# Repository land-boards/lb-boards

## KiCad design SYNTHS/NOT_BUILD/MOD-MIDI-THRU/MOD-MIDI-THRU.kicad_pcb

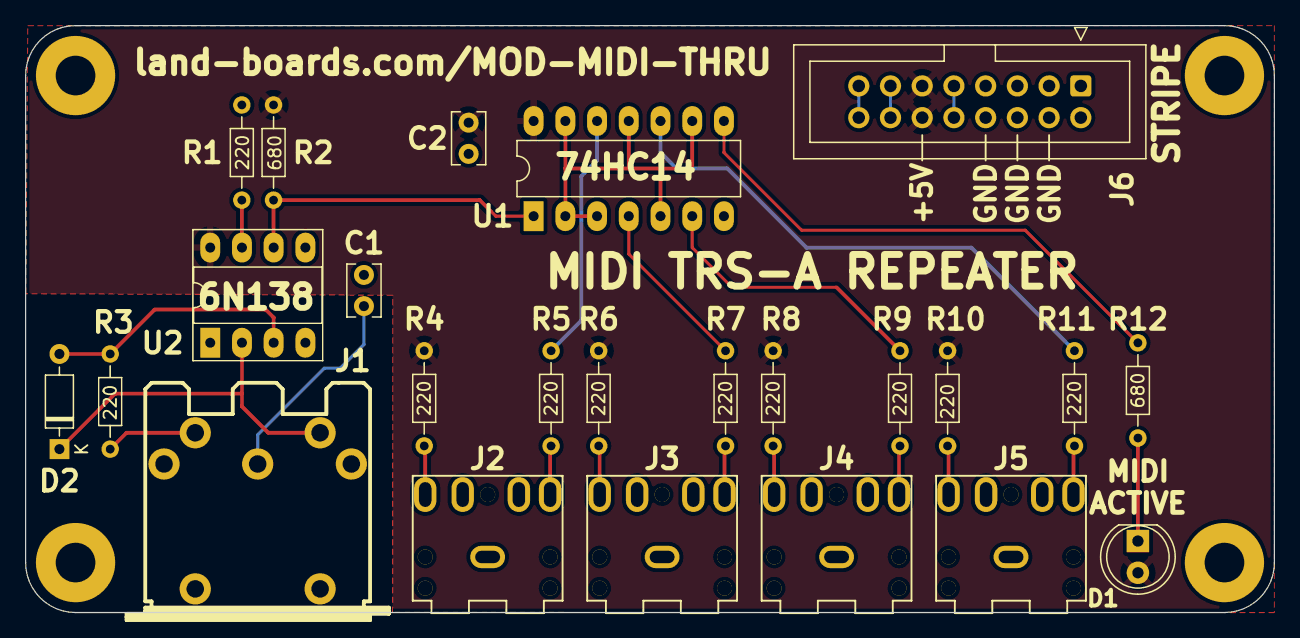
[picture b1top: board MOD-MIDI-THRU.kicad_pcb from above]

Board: 2 copper layers, 100.0 x 47.0 mm, 28 parts (0 on the bottom side), 26 nets.

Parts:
C1, C2: 0.1uF; C_Rect_L4.0mm_W2.5mm_P2.50mm
D1: LED; LED_D5.0mm
D2: 1N914; D_DO-35_SOD27_P7.62mm_Horizontal
J1: DIN-5; MIDI_DIN-5
J2, J3, J4, J5: AudioJack3; Jack_3.5mm_CUI_SJ1-3523N_Horizontal
J6: Conn_02x08_Odd_Even; IDC-Header_2x08_P2.54mm_Vertical
MTG1, MTG2, MTG3, MTG4: MountingHole; MTG-4-40
R1, R3, R4, R5, R6, R7, R8, R9, R10, R11: 220; R_Axial_DIN0204_L3.6mm_D1.6mm_P7.62mm_Horizontal
R2, R12: 680; R_Axial_DIN0204_L3.6mm_D1.6mm_P7.62mm_Horizontal
U1: 74HC14; DIP-14_W7.62mm_LongPads
U2: 6N138; DIP-8_W7.62mm_Socket_LongPads

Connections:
+5V: C2.1, D1.2 (A), J6.11, J6.12, R2.1, R4.1, R6.1, R8.1, R10.1, U1.14 (VCC), U2.8 (VCC)
+12V: J6.9, J6.10
/CV_OUT: J6.13, J6.14
/GATE_OUT: J6.15, J6.16
/MIDI_1_OUT: J2.T, R5.2
/MIDI_1_PWR: J2.R, R4.2
/MIDI_2_OUT: J3.T, R7.2
/MIDI_2_PWR: J3.R, R6.2
/MIDI_3_OUT: J4.T, R9.2
/MIDI_3_PWR: J4.R, R8.2
/MIDI_4_OUT: J5.T, R11.2
/MIDI_4_PWR: J5.R, R10.2
/MIDI_IN: D2.1 (K), J1.4, U2.2 (C1)
/MIDI_RTN: J1.5, R3.2
/RXD: R2.2, U1.1, U2.6 (VO2)
GND: C1.2, C2.2, J2.S, J3.S, J4.S, J5.S, J6.3, J6.4, J6.5, J6.6, J6.7, J6.8, R1.2, U1.7 (GND), U2.5 (GND)
unnamed: C1.1, J1.2
unnamed: D1.1 (K), R12.2
unnamed: D2.2 (A), R3.1, U2.3 (C2)
unnamed: R1.1, U2.7 (VO1)
unnamed: R5.1, U1.12
unnamed: R7.1, U1.4
unnamed: R9.1, U1.6
unnamed: R11.1, U1.10
unnamed: R12.1, U1.8
unnamed: U1.2, U1.3, U1.5, U1.9, U1.11, U1.13

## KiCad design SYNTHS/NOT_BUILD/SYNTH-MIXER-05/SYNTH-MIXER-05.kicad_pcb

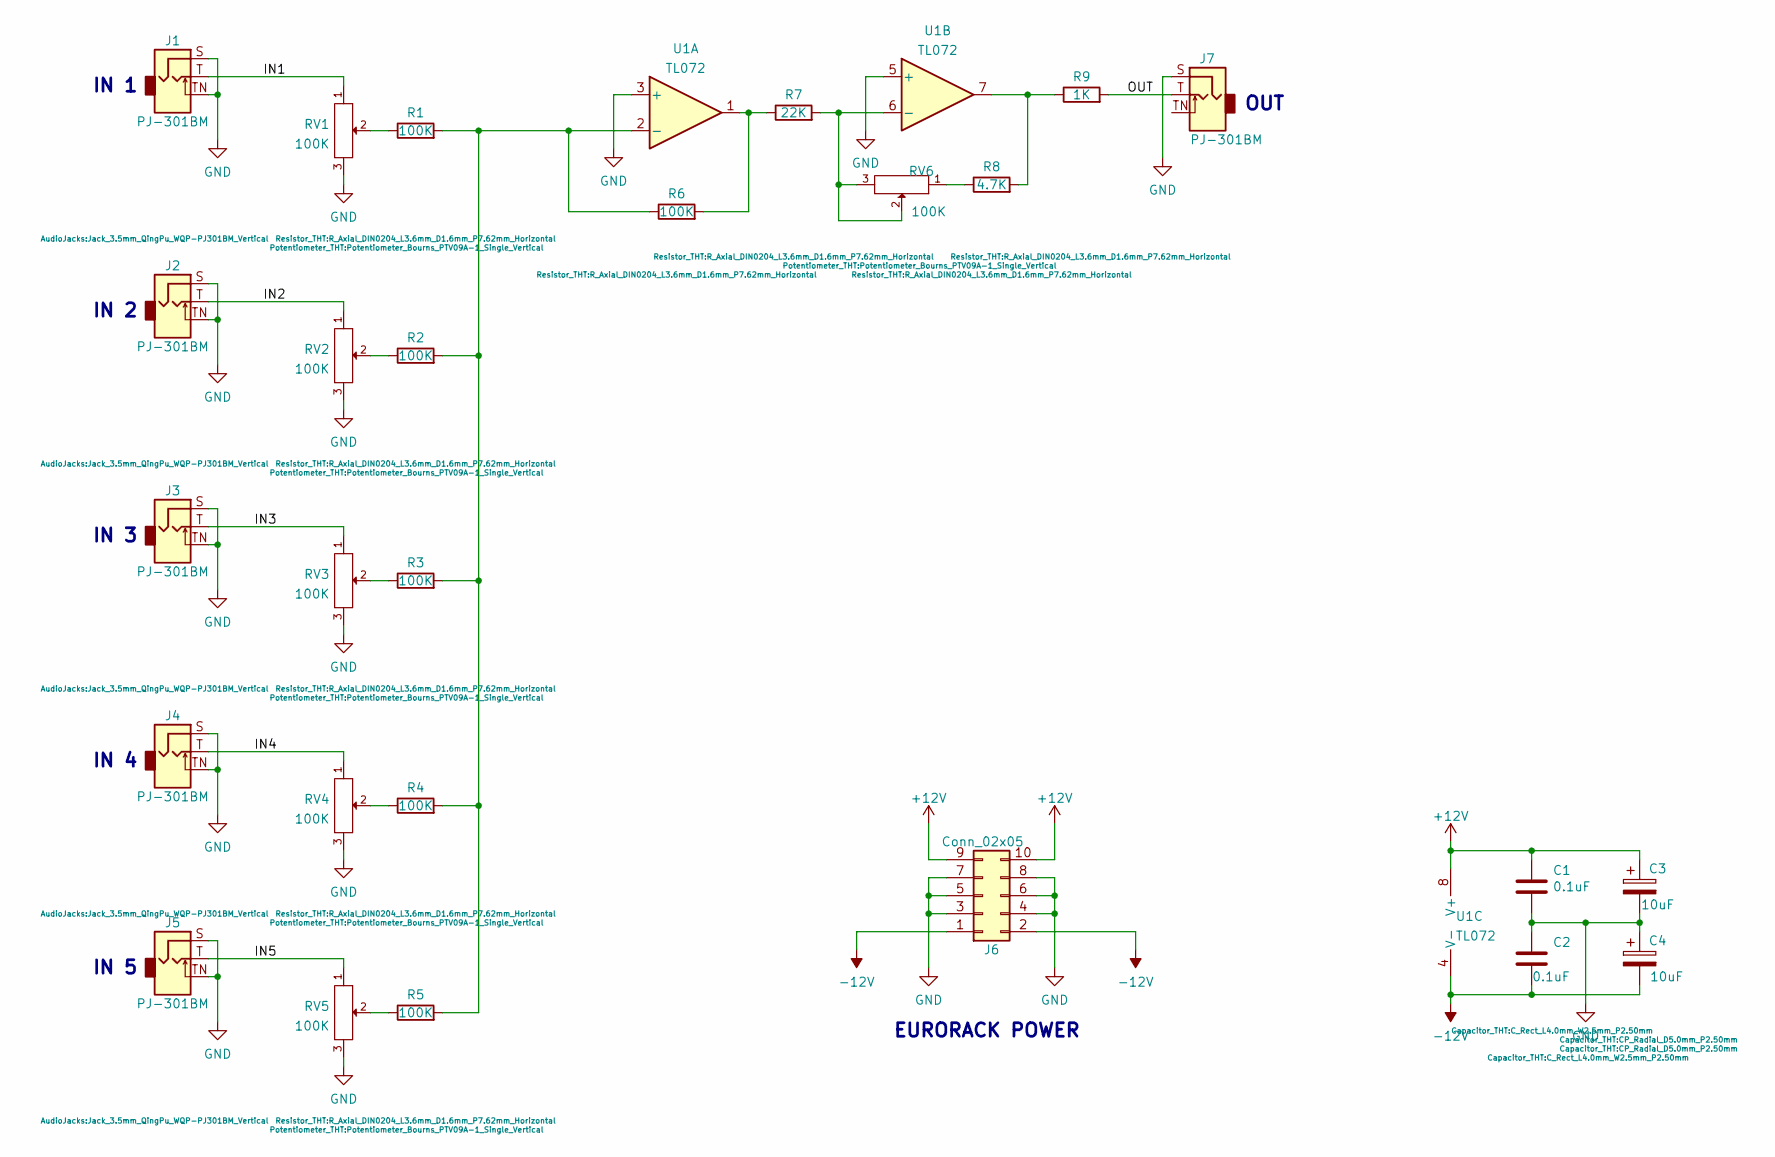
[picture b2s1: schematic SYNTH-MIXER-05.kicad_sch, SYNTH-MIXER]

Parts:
C1, C2: 0.1uF; C_Rect_L4.0mm_W2.5mm_P2.50mm
C3, C4: 10uF; CP_Radial_D5.0mm_P2.50mm
J1, J2, J3, J4, J5, J7: PJ-301BM; Jack_3.5mm_QingPu_WQP-PJ301BM_Vertical
J6: Conn_02x05; IDC-Header_2x05_P2.54mm_Vertical
R1, R2, R3, R4, R5, R6: 100K; R_Axial_DIN0204_L3.6mm_D1.6mm_P7.62mm_Horizontal
R7: 22K; R_Axial_DIN0204_L3.6mm_D1.6mm_P7.62mm_Horizontal
R8: 4.7K; R_Axial_DIN0204_L3.6mm_D1.6mm_P7.62mm_Horizontal
R9: 1K; R_Axial_DIN0204_L3.6mm_D1.6mm_P7.62mm_Horizontal
RV1, RV2, RV3, RV4, RV5, RV6: 100K; Potentiometer_Bourns_PTV09A-1_Single_Vertical
U1: TL072; DIP-8_W7.62mm

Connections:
+12V: C1.1, C3.1, J6.9, J6.10, U1.8 (V+)
-12V: C2.2, C4.2, J6.1, J6.2, U1.4 (V-)
/IN1: J1.T, RV1.1
/IN2: J2.T, RV2.1
/IN3: J3.T, RV3.1
/IN4: J4.T, RV4.1
/IN5: J5.T, RV5.1
/OUT: J7.T, R9.2
GND: C1.2, C2.1, C3.2, C4.1, J1.S, J1.TN, J2.S, J2.TN, J3.S, J3.TN, J4.S, J4.TN, J5.S, J5.TN, J6.3, J6.4, J6.5, J6.6, J6.7, J6.8, J7.S, RV1.3, RV2.3, RV3.3, RV4.3, RV5.3, U1.3 (+), U1.5 (+)
unnamed: R1.1, RV1.2
unnamed: R1.2, R2.2, R3.2, R4.2, R5.2, R6.1, U1.2 (-)
unnamed: R2.1, RV2.2
unnamed: R3.1, RV3.2
unnamed: R4.1, RV4.2
unnamed: R5.1, RV5.2
unnamed: R6.2, R7.1, U1.1
unnamed: R7.2, RV6.2, RV6.3, U1.6 (-)
unnamed: R8.1, RV6.1
unnamed: R8.2, R9.1, U1.7

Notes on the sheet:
IN 5
IN 1
IN 3
IN 4
EURORACK POWER
OUT
IN 2

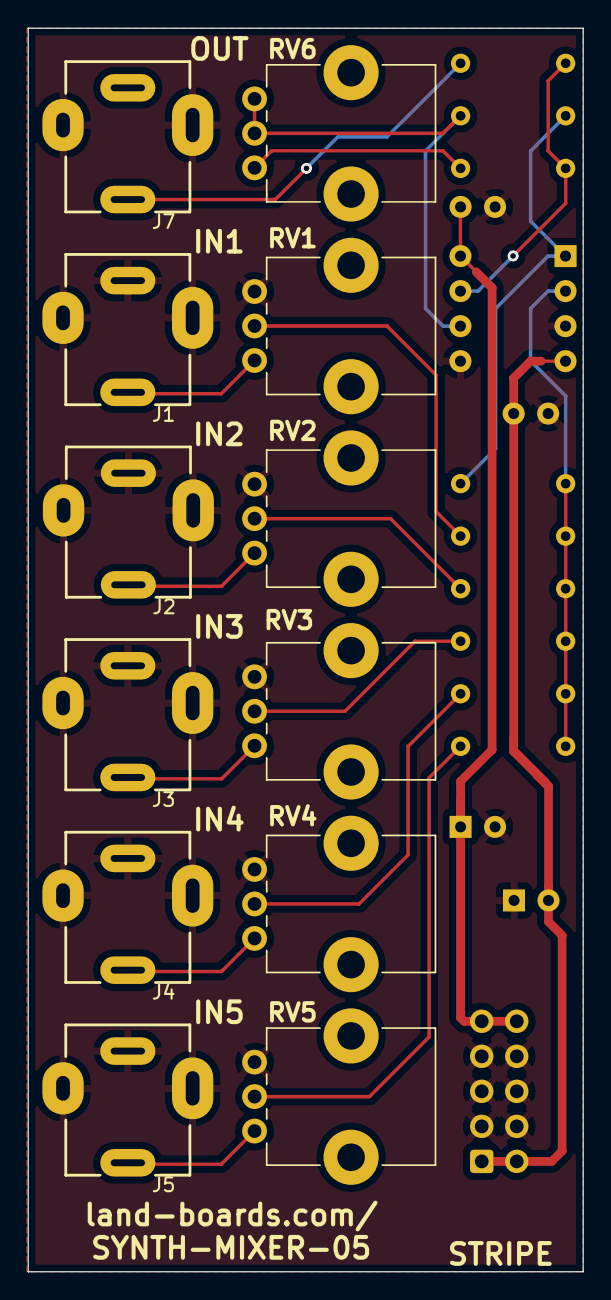
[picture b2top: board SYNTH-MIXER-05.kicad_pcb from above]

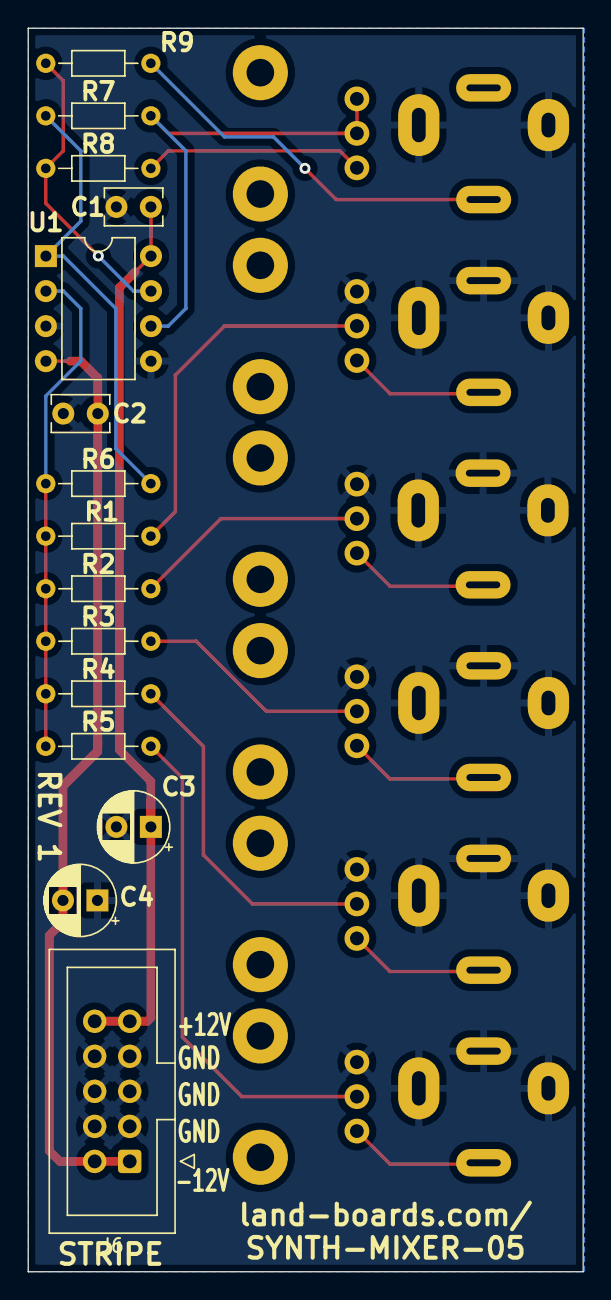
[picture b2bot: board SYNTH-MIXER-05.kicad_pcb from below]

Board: 2 copper layers, 40.2 x 90.2 mm, 27 parts (15 on the bottom side), 19 nets.

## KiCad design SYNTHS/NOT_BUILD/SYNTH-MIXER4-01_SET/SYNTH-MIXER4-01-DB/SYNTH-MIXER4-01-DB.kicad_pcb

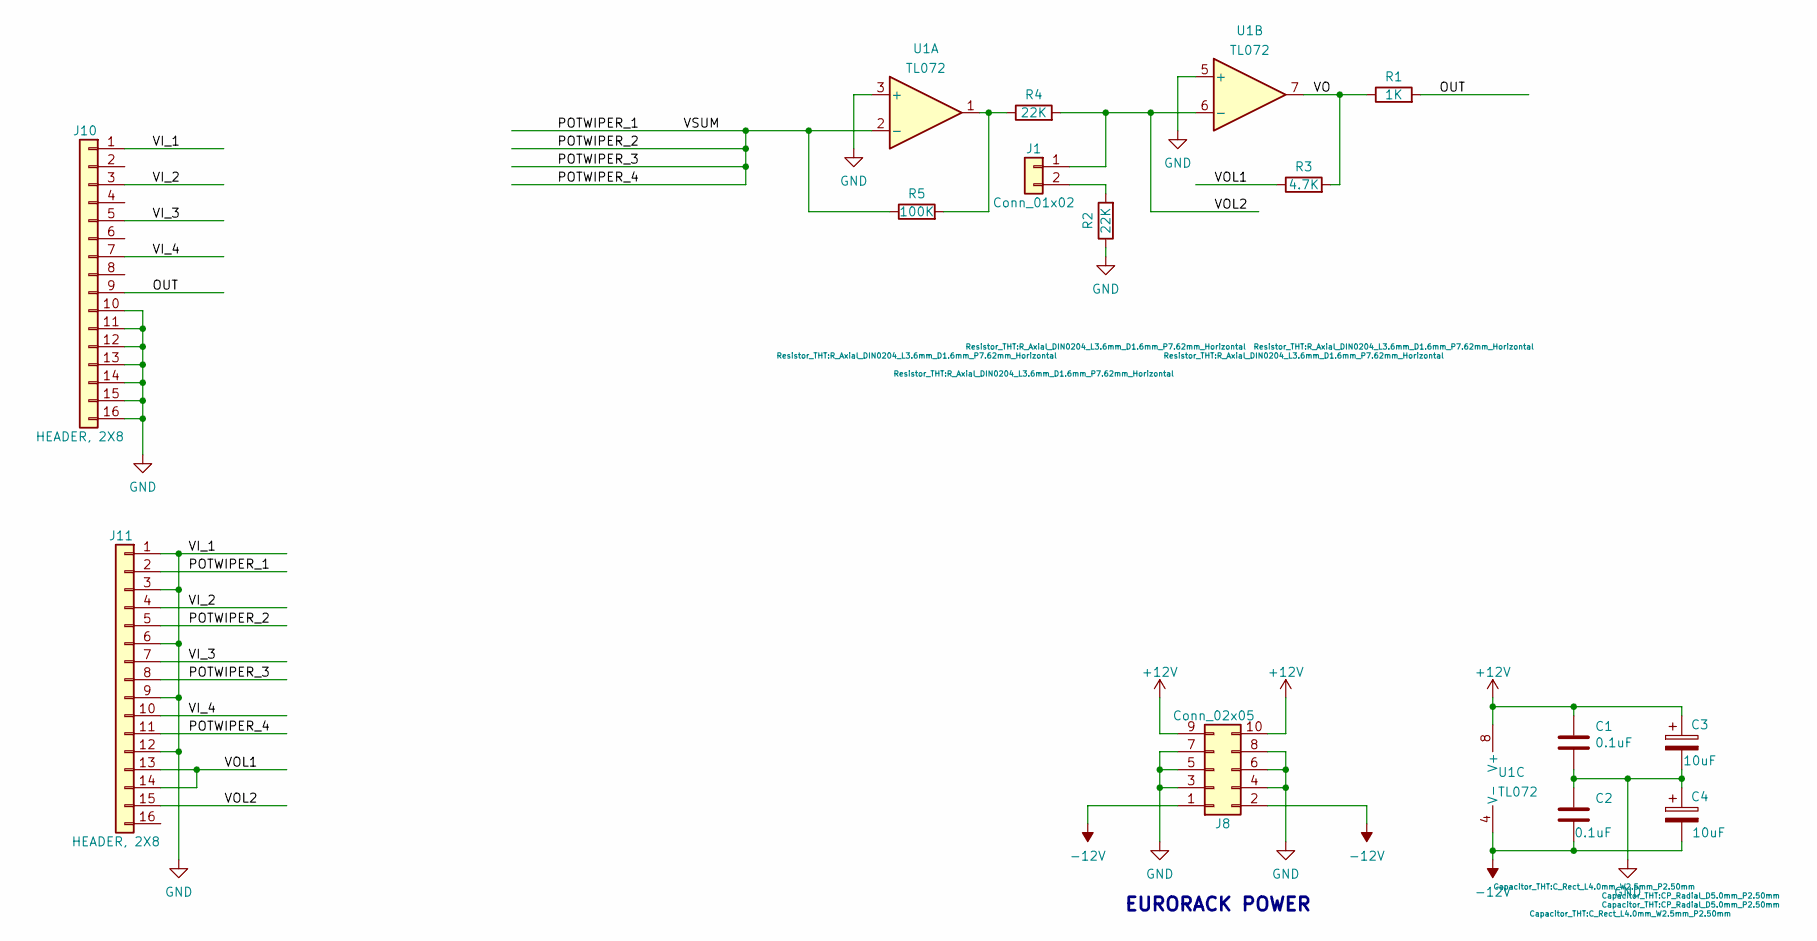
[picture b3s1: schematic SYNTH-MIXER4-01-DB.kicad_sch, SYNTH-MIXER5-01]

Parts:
C1, C2: 0.1uF; C_Rect_L4.0mm_W2.5mm_P2.50mm
C3, C4: 10uF; CP_Radial_D5.0mm_P2.50mm
J1: Conn_01x02; PinHeader_1x02_P2.54mm_Horizontal
J8: Conn_02x05; IDC-Header_2x05_P2.54mm_Vertical
J10, J11: HEADER, 2X8; PinHeader_2x08_P2.54mm_Vertical
R1: 1K; R_Axial_DIN0204_L3.6mm_D1.6mm_P7.62mm_Horizontal
R2, R4: 22K; R_Axial_DIN0204_L3.6mm_D1.6mm_P7.62mm_Horizontal
R3: 4.7K; R_Axial_DIN0204_L3.6mm_D1.6mm_P7.62mm_Horizontal
R5: 100K; R_Axial_DIN0204_L3.6mm_D1.6mm_P7.62mm_Horizontal
U1: TL072; DIP-8_W7.62mm

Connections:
+12V: C1.1, C3.1, J8.9, J8.10, U1.8 (V+)
-12V: C2.2, C4.2, J8.1, J8.2, U1.4 (V-)
/OUT: J10.9, R1.2
/POTWIPER_1: J11.2, J11.5, J11.8, J11.11, R5.1, U1.2 (-)
/VI_2: J10.3, J11.4
/VI_3: J10.5, J11.7
/VI_4: J10.7, J11.10
/VO: R1.1, R3.2, U1.7
/VOL1: J11.13, J11.14, R3.1
/VOL2: J1.1, J11.15, R4.2, U1.6 (-)
GND: C1.2, C2.1, C3.2, C4.1, J8.3, J8.4, J8.5, J8.6, J8.7, J8.8, J10.1, J10.10, J10.11, J10.12, J10.13, J10.14, J10.15, J10.16, J11.1, J11.3, J11.6, J11.9, J11.12, R2.1, U1.3 (+), U1.5 (+)
unnamed: J1.2, R2.2
unnamed: R4.1, R5.2, U1.1

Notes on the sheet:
EURORACK POWER

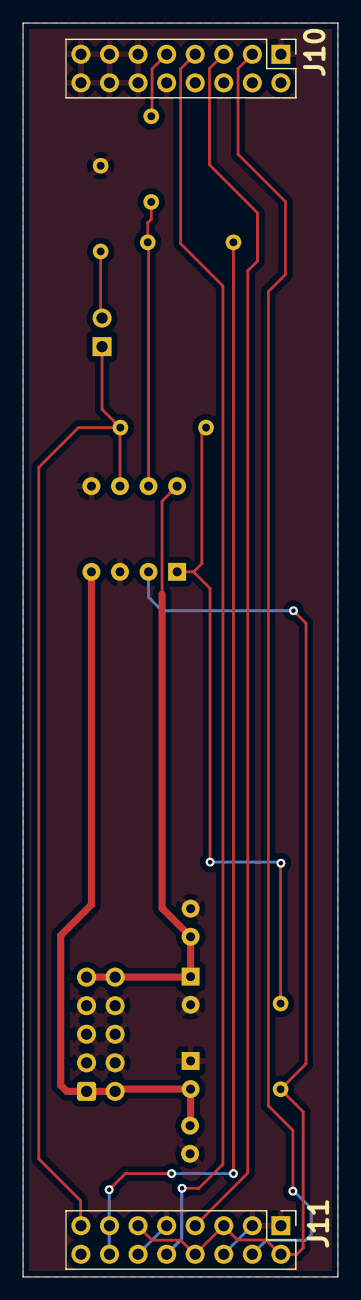
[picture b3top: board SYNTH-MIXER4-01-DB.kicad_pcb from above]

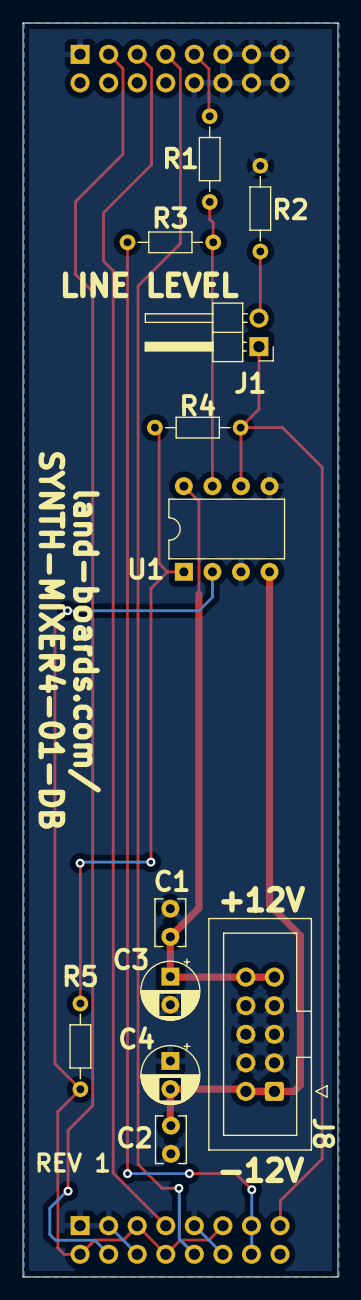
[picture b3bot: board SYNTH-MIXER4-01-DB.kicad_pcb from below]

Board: 2 copper layers, 28.0 x 111.5 mm, 14 parts (12 on the bottom side), 13 nets.

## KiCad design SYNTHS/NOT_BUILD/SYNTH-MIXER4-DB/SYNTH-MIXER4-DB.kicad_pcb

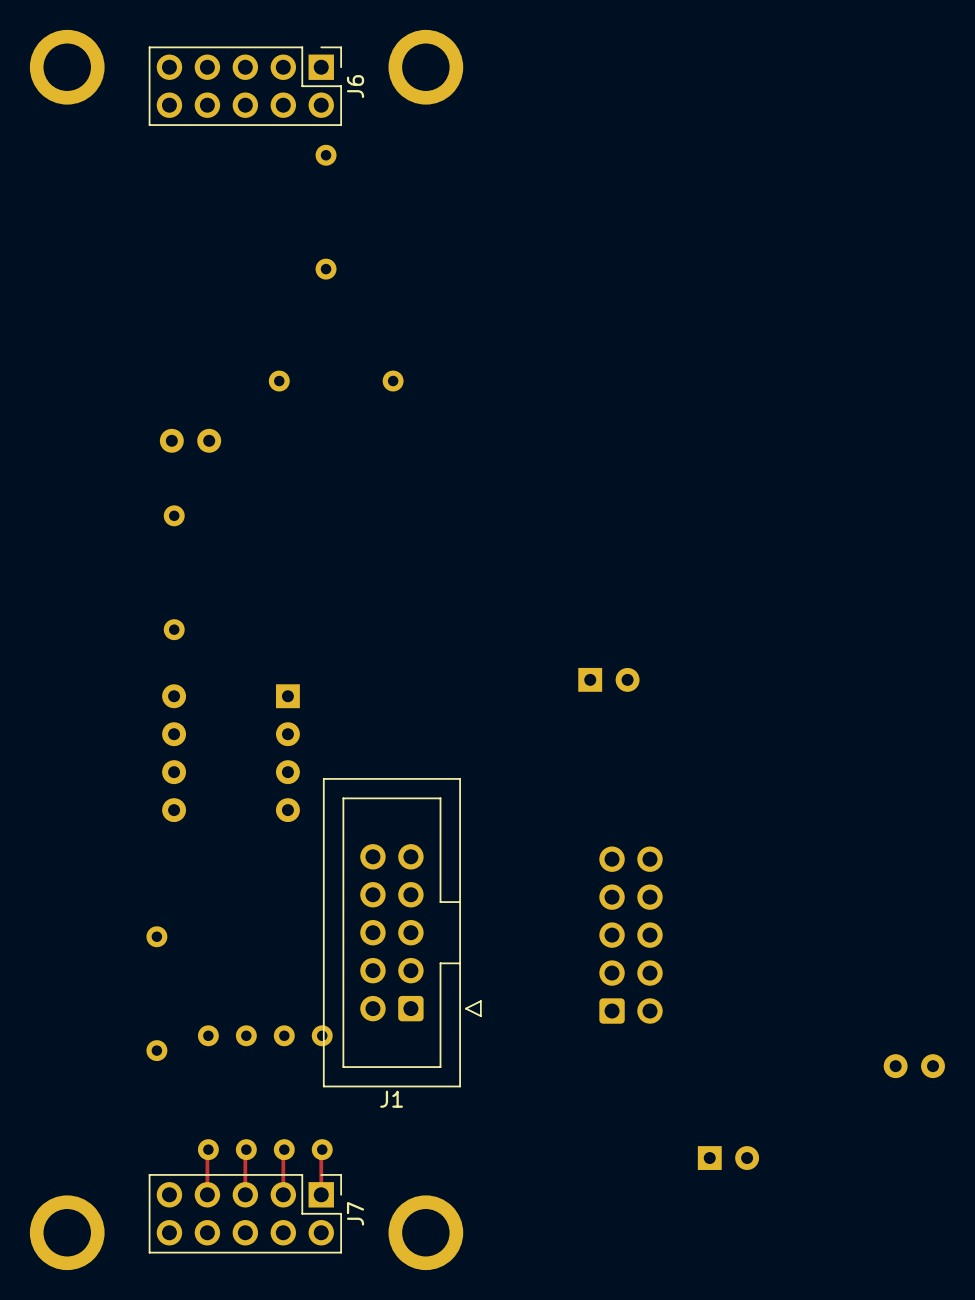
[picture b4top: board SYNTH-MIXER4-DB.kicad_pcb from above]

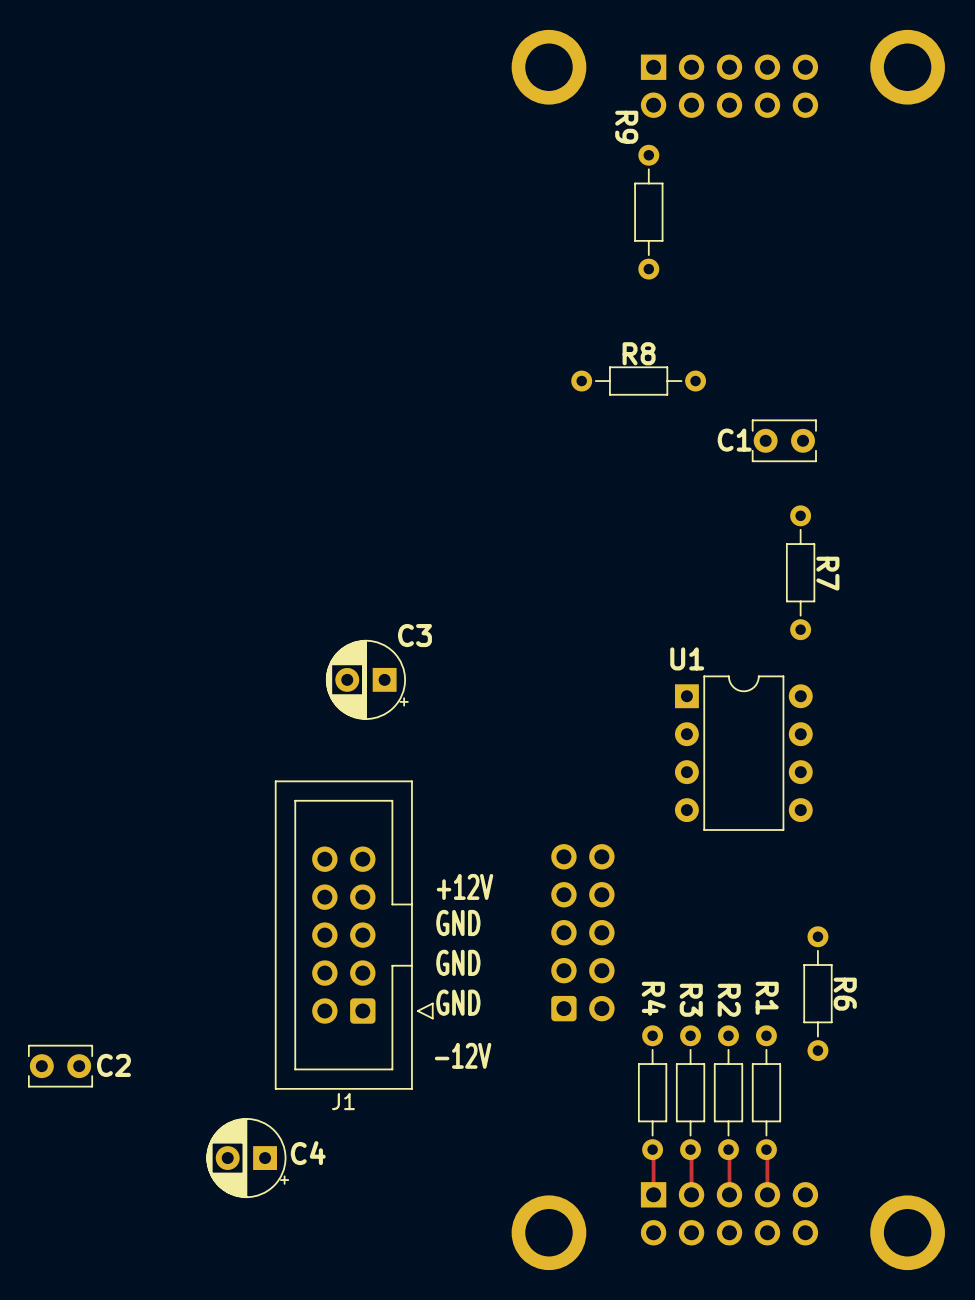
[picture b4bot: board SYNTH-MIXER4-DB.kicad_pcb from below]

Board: 2 copper layers, 21 parts (14 on the bottom side), 17 nets.

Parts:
C1, C2: 0.1uF; C_Rect_L4.0mm_W2.5mm_P2.50mm
C3, C4: 10uF; CP_Radial_D5.0mm_P2.50mm
J1, J1#2: Conn_02x05; IDC-Header_2x05_P2.54mm_Vertical
J6, J7: Conn_01x10; PinHeader_2x05_P2.54mm_Vertical
MTG1, MTG2, MTG3, MTG4: MountingHole; MTG-4-40-SMALL
R1, R2, R3, R4, R6: 100K; R_Axial_DIN0204_L3.6mm_D1.6mm_P7.62mm_Horizontal
R7: 22K; R_Axial_DIN0204_L3.6mm_D1.6mm_P7.62mm_Horizontal
R8: 4.7K; R_Axial_DIN0204_L3.6mm_D1.6mm_P7.62mm_Horizontal
R9: 1K; R_Axial_DIN0204_L3.6mm_D1.6mm_P7.62mm_Horizontal
U1: TL072; DIP-8_W7.62mm

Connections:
+12V: C1.1, C3.1, J1.1, J1.2, J1#2.1, J1#2.2, U1.8 (V+)
-12V: C2.2, C4.2, J1.9, J1.10, J1#2.9, J1#2.10, U1.4 (V-)
/IN1: J6.4, J7.8
/IN2: J6.6, J7.6
/IN3: J6.8, J7.4
/IN4: J6.10, J7.2
/OUT: J6.2, R9.2
/RW1: J7.7, R1.1
/RW2: J7.5, R2.1
/RW3: J7.3, R3.1
/RW4: J7.1, R4.1
/VOL1: J7.10, R8.1
/VOL2: J7.9, R7.2, U1.6 (-)
GND: C1.2, C2.1, C3.2, C4.1, J1.3, J1.4, J1.5, J1.6, J1.7, J1.8, J1#2.3, J1#2.4, J1#2.5, J1#2.6, J1#2.7, J1#2.8, J6.1, J6.3, J6.5, J6.7, J6.9, U1.3 (+), U1.5 (+)
unnamed: R1.2, R2.2, R3.2, R4.2, R6.1, U1.2 (-)
unnamed: R6.2, R7.1, U1.1
unnamed: R8.2, R9.1, U1.7

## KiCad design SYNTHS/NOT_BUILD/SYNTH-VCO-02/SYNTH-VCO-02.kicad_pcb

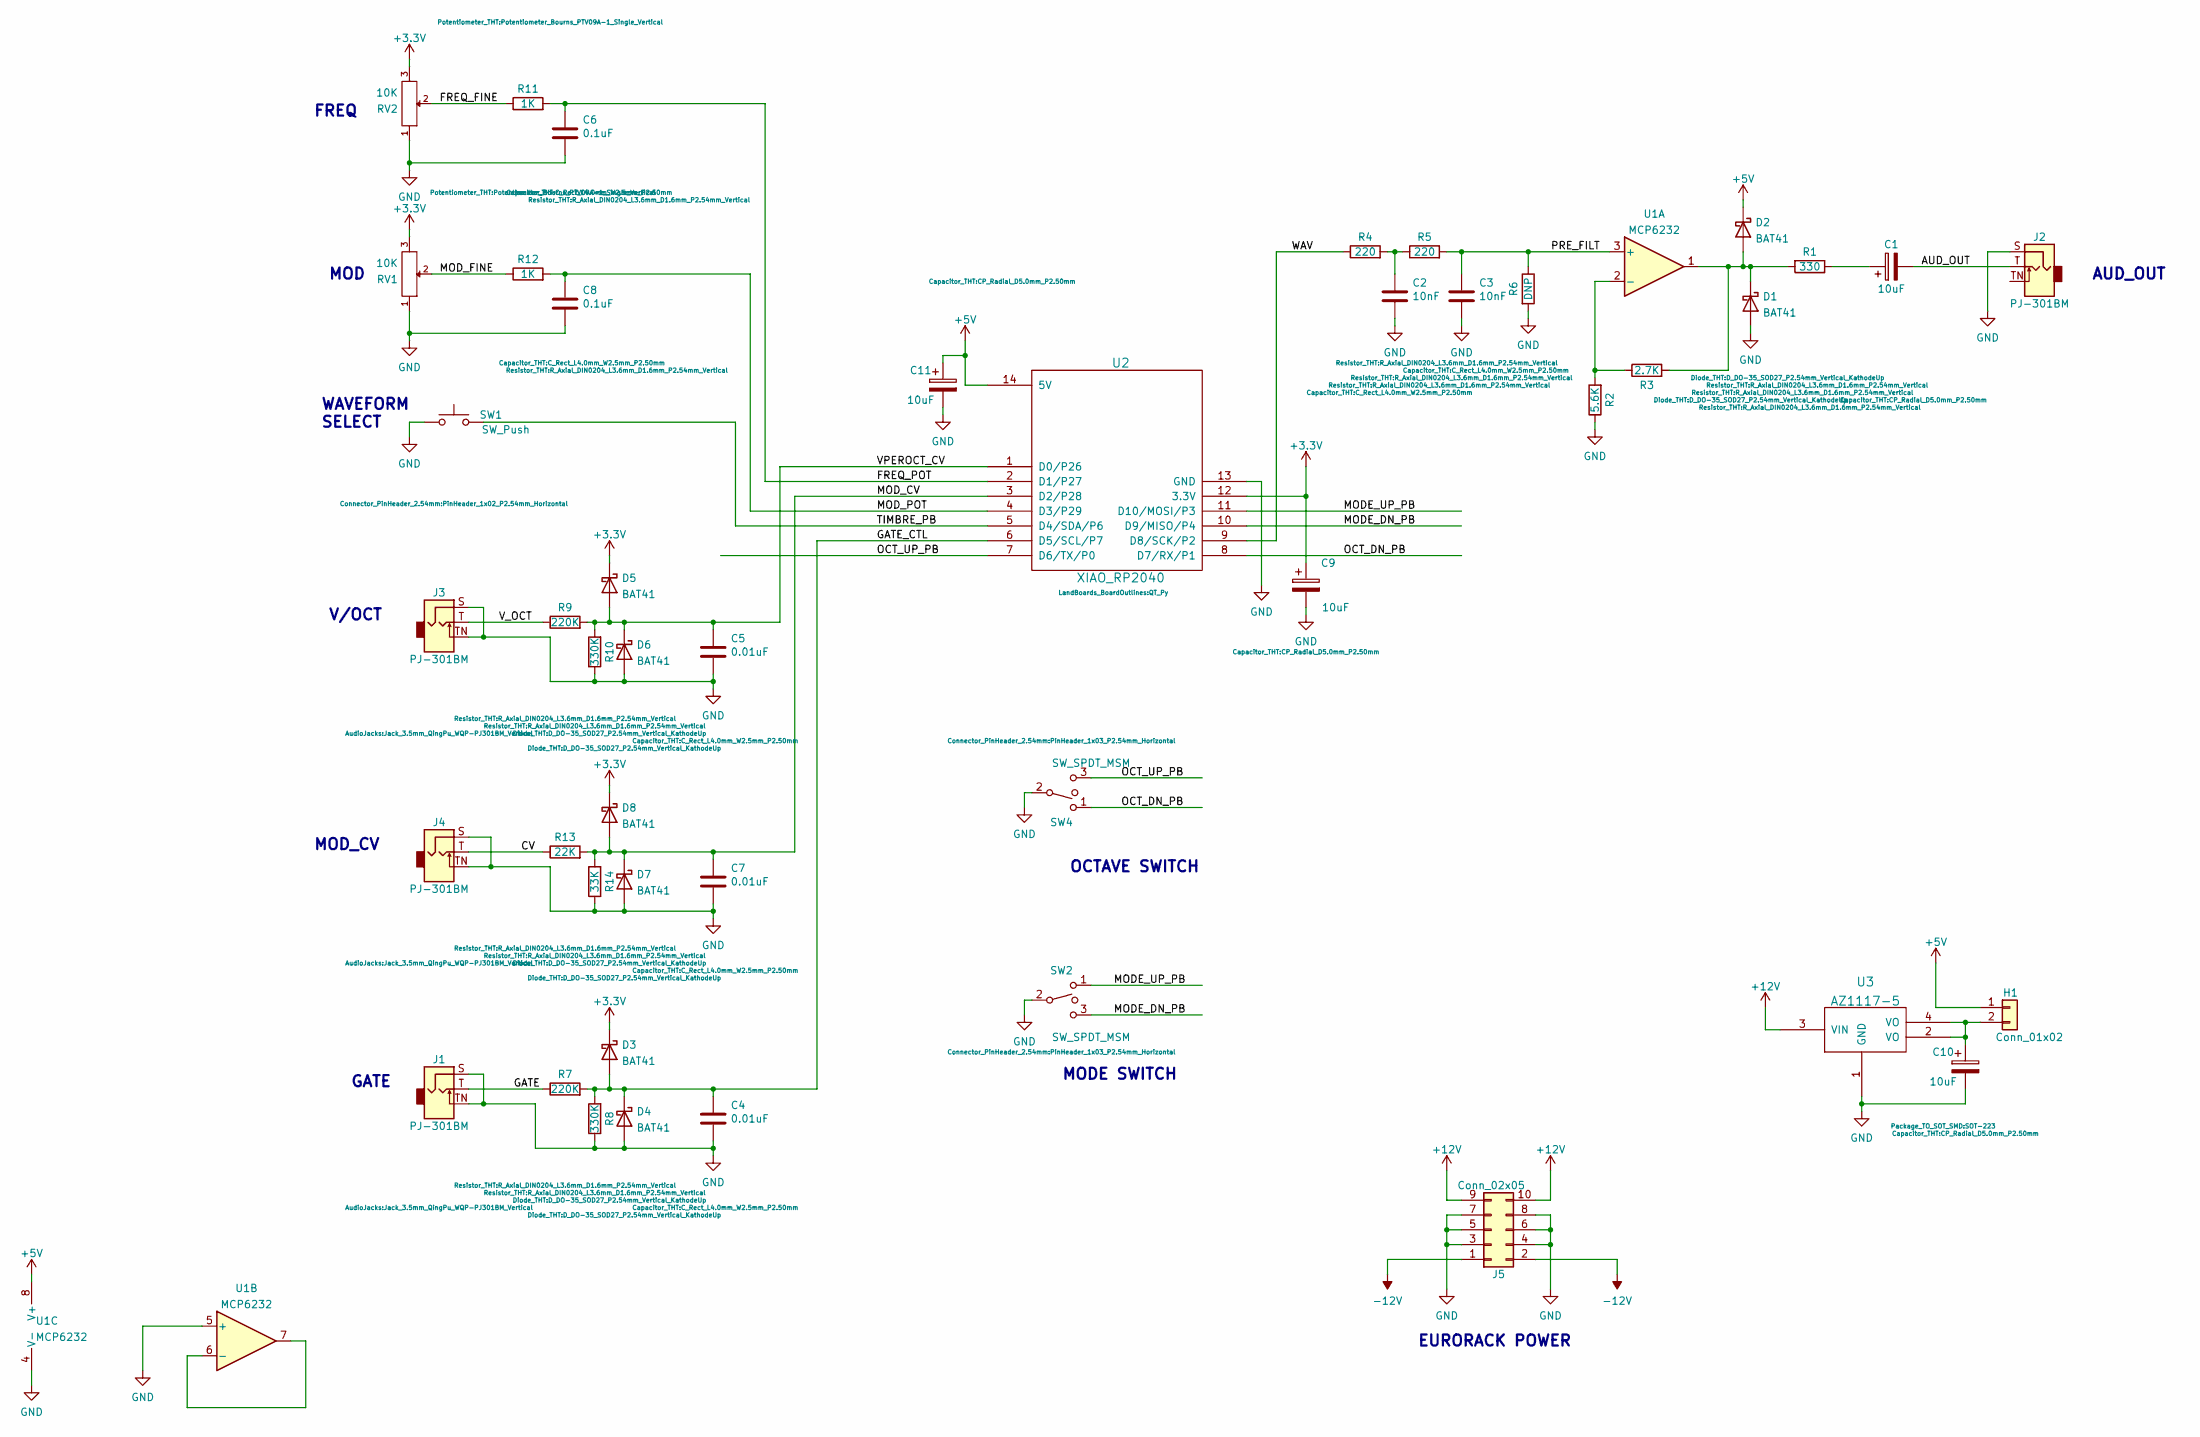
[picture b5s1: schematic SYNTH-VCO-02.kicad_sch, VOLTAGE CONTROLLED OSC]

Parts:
C1, C9, C10, C11: 10uF; CP_Radial_D5.0mm_P2.50mm
C2, C3: 10nF; C_Rect_L4.0mm_W2.5mm_P2.50mm
C4, C5, C7: 0.01uF; C_Rect_L4.0mm_W2.5mm_P2.50mm
C6, C8: 0.1uF; C_Rect_L4.0mm_W2.5mm_P2.50mm
D1, D2, D3, D4, D5, D6, D7, D8: BAT41; D_DO-35_SOD27_P2.54mm_Vertical_KathodeUp
H1: Conn_01x02; PinHeader_1x02_P2.54mm_Vertical
J1, J2, J3, J4: PJ-301BM; Jack_3.5mm_QingPu_WQP-PJ301BM_Vertical
J5: Conn_02x05; IDC-Header_2x05_P2.54mm_Vertical
R1: 330; R_Axial_DIN0204_L3.6mm_D1.6mm_P2.54mm_Vertical
R2: 5.6K; R_Axial_DIN0204_L3.6mm_D1.6mm_P2.54mm_Vertical
R3: 2.7K; R_Axial_DIN0204_L3.6mm_D1.6mm_P2.54mm_Vertical
R4, R5: 220; R_Axial_DIN0204_L3.6mm_D1.6mm_P2.54mm_Vertical
R6: DNP; R_Axial_DIN0204_L3.6mm_D1.6mm_P2.54mm_Vertical
R7, R9: 220K; R_Axial_DIN0204_L3.6mm_D1.6mm_P2.54mm_Vertical
R8, R10: 330K; R_Axial_DIN0204_L3.6mm_D1.6mm_P2.54mm_Vertical
R11, R12: 1K; R_Axial_DIN0204_L3.6mm_D1.6mm_P2.54mm_Vertical
R13: 22K; R_Axial_DIN0204_L3.6mm_D1.6mm_P2.54mm_Vertical
R14: 33K; R_Axial_DIN0204_L3.6mm_D1.6mm_P2.54mm_Vertical
RV1, RV2: 10K; Potentiometer_Bourns_PTV09A-1_Single_Vertical
SW1: SW_Push; PinHeader_1x02_P2.54mm_Horizontal
SW2, SW4: SW_SPDT_MSM; PinHeader_1x03_P2.54mm_Horizontal
U1: MCP6232; DIP-8_W7.62mm
U2: XIAO_RP2040; QT_Py
U3: AZ1117-5; SOT-223

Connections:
+3V3: C9.1, D3.1 (K), D5.1 (K), D8.1 (K), RV1.3, RV2.3, U2.12 (3.3V)
+5V: C11.1, D2.1 (K), H1.1, U1.8 (V+), U2.14 (5V)
+12V: J5.9, J5.10, U3.3 (VIN)
-12V: J5.1, J5.2
/AUD_OUT: C1.2, J2.T
/CV: J4.T, R13.1
/FREQ_FINE: R11.1, RV2.2
/FREQ_POT: C6.1, R11.2, U2.2 (D1/P27)
/GATE: J1.T, R7.1
/GATE_CTL: C4.1, D3.2 (A), D4.1 (K), R7.2, R8.2, U2.6 (D5/SCL/P7)
/MODE_DN_PB: SW2.3, U2.10 (D9/MISO/P4)
/MODE_UP_PB: SW2.1, U2.11 (D10/MOSI/P3)
/MOD_CV: C7.1, D7.1 (K), D8.2 (A), R13.2, R14.2, U2.3 (D2/P28)
/MOD_FINE: R12.1, RV1.2
/MOD_POT: C8.1, R12.2, U2.4 (D3/P29)
/OCT_DN_PB: SW4.1, U2.8 (D7/RX/P1)
/OCT_UP_PB: SW4.3, U2.7 (D6/TX/P0)
/PRE_FILT: C3.1, R5.2, R6.1, U1.3 (+)
/TIMBRE_PB: SW1.2, U2.5 (D4/SDA/P6)
/VPEROCT_CV: C5.1, D5.2 (A), D6.1 (K), R9.2, R10.2, U2.1 (D0/P26)
/V_OCT: J3.T, R9.1
/WAV: R4.1, U2.9 (D8/SCK/P2)
GND: C2.2, C3.2, C4.2, C5.2, C6.2, C7.2, C8.2, C9.2, C10.2, C11.2, D1.2 (A), D4.2 (A), D6.2 (A), D7.2 (A), J1.S, J1.TN, J2.S, J3.S, J3.TN, J4.S, J4.TN, J5.3, J5.4, J5.5, J5.6, J5.7, J5.8, R2.1, R6.2, R8.1, R10.1, R14.1, RV1.1, RV2.1, SW1.1, SW2.2, SW4.2, U1.4 (V-), U1.5 (+), U2.13 (GND), U3.1 (GND)
unnamed: C1.1, R1.1
unnamed: C2.1, R4.2, R5.1
unnamed: C10.1, H1.2, U3.2 (VO), U3.4 (VO)
unnamed: D1.1 (K), D2.2 (A), R1.2, R3.2, U1.1
unnamed: R2.2, R3.1, U1.2 (-)
unnamed: U1.6 (-), U1.7

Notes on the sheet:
OCTAVE SWITCH
AUD_OUT
GATE
V/OCT
EURORACK POWER
MOD_CV
FREQ
MODE SWITCH
WAVEFORM SELECT
MOD

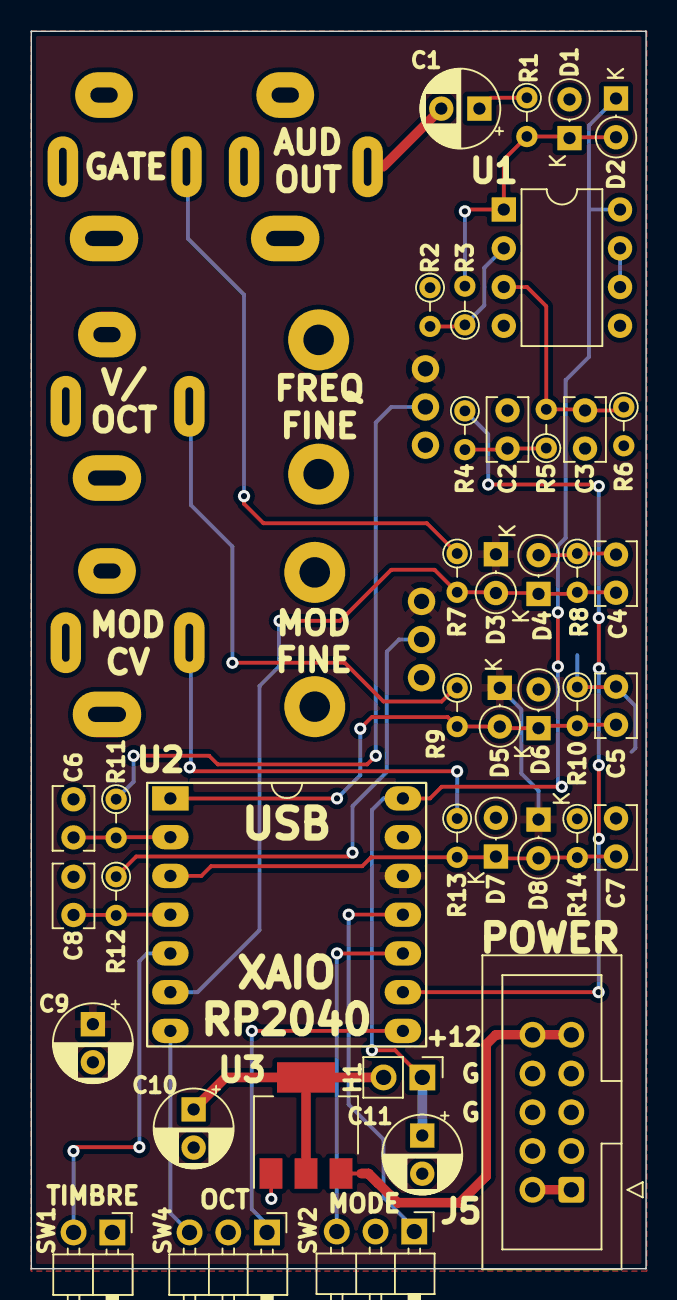
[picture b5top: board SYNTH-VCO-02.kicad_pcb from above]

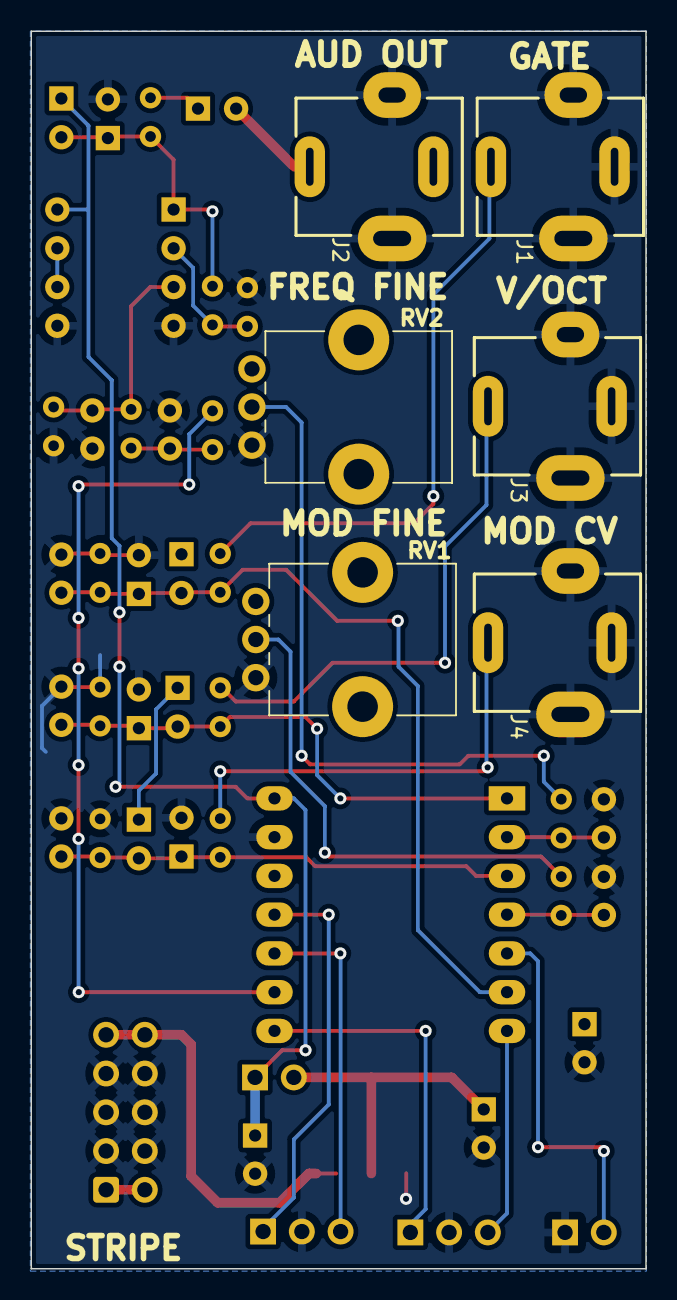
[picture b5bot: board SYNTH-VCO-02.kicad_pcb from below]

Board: 2 copper layers, 40.3 x 81.1 mm, 47 parts (6 on the bottom side), 29 nets.

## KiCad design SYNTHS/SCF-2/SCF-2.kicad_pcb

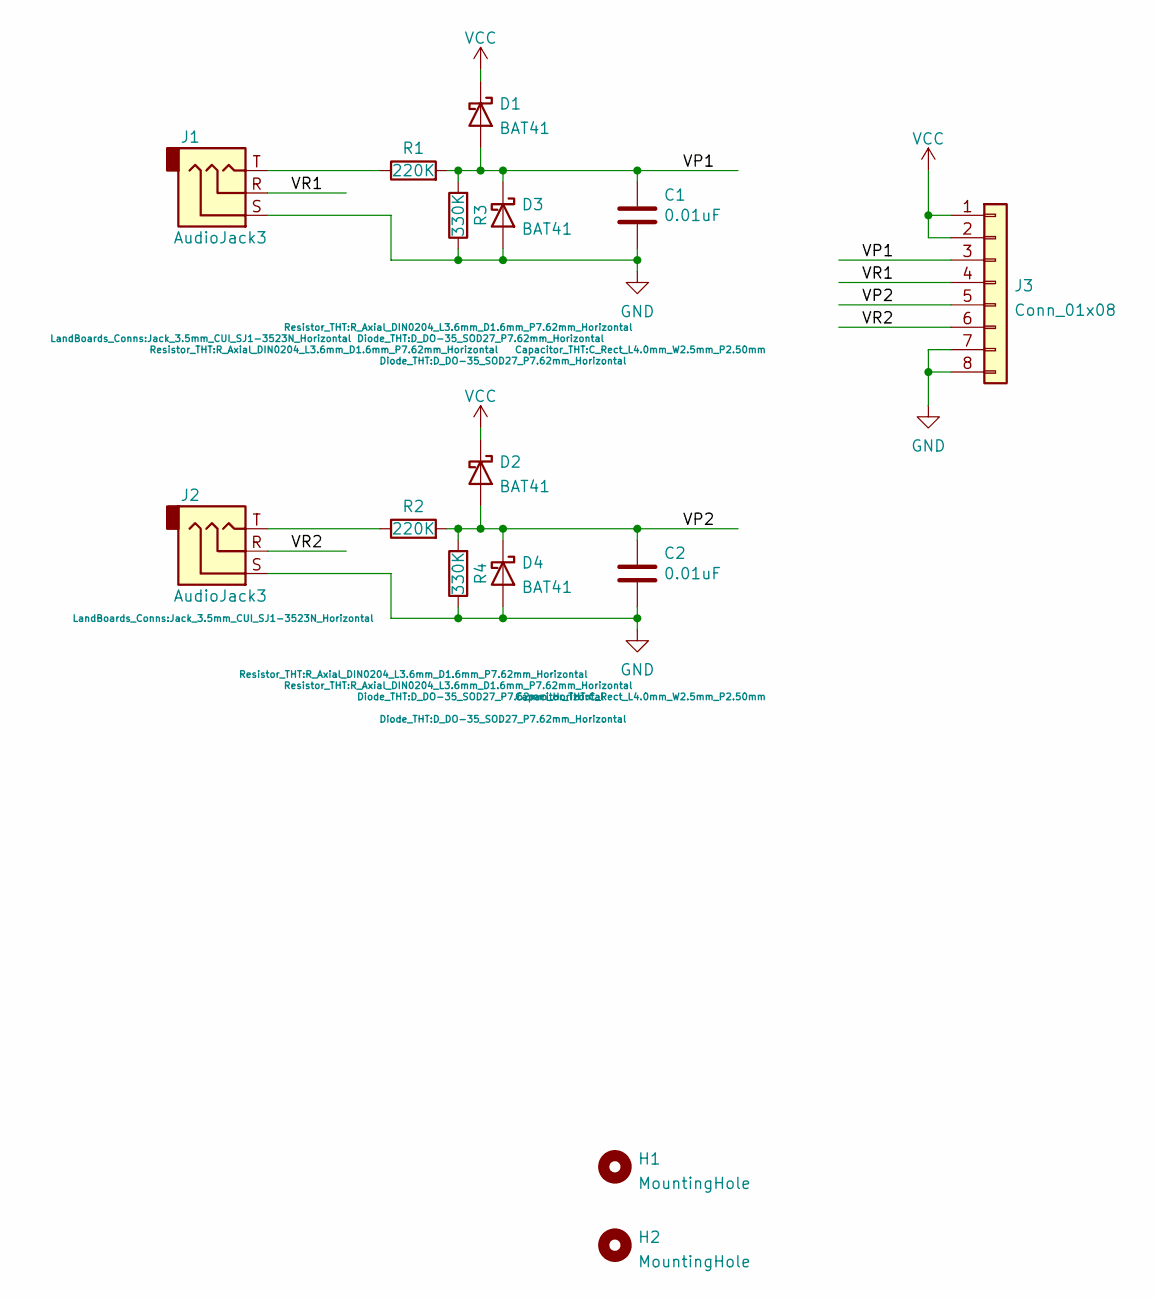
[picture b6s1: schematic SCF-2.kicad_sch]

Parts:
C1, C2: 0.01uF; C_Rect_L4.0mm_W2.5mm_P2.50mm
D1, D2, D3, D4: BAT41; D_DO-35_SOD27_P7.62mm_Horizontal
H1, H2: MountingHole; MTG-4-40-SMALL
J1, J2: AudioJack3; Jack_3.5mm_CUI_SJ1-3523N_Horizontal
J3: Conn_01x08; PinHeader_2x04_P2.54mm_Horizontal
R1, R2: 220K; R_Axial_DIN0204_L3.6mm_D1.6mm_P7.62mm_Horizontal
R3, R4: 330K; R_Axial_DIN0204_L3.6mm_D1.6mm_P7.62mm_Horizontal

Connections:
/VP1: C1.1, D1.2 (A), D3.1 (K), J3.3, R1.2, R3.2
/VP2: C2.1, D2.2 (A), D4.1 (K), J3.5, R2.2, R4.2
/VS1: J1.R, J3.4
/VS2: J2.R, J3.6
GND: C1.2, C2.2, D3.2 (A), D4.2 (A), J1.S, J2.S, J3.7, J3.8, R3.1, R4.1
unnamed: J1.T, R1.1
unnamed: J2.T, R2.1
VCC: D1.1 (K), D2.1 (K), J3.1, J3.2

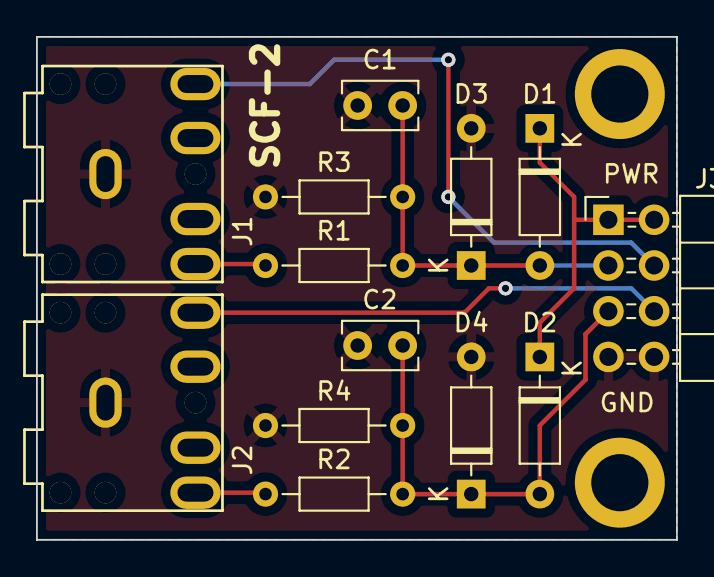
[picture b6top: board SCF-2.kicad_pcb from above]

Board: 2 copper layers, 35.6 x 27.9 mm, 15 parts (0 on the bottom side), 8 nets.

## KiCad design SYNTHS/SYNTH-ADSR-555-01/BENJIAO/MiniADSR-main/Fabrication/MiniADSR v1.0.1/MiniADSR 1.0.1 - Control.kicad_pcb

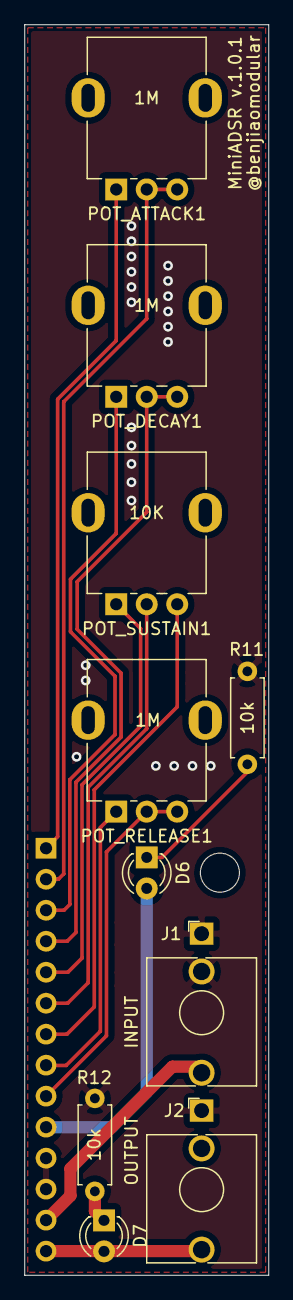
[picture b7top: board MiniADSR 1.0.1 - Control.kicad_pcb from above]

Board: 2 copper layers, 20.0 x 102.5 mm, 11 parts (1 on the bottom side), 15 nets.

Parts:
D6: PWR_LED; LED_D3.0mm
D7: OUTPUT_LED; LED_D3.0mm
J1: INPUT; AudioJack_3.5mm
J2: OUTPUT; AudioJack_3.5mm
J4: ControlBoard_Pins; PinSocket_1x14_P2.54mm_Vertical
POT_ATTACK1: 1M; Potentiometer_RV09
POT_DECAY1: 1M; Potentiometer_RV09
POT_RELEASE1: 1M; Potentiometer_RV09
POT_SUSTAIN1: 10K; Potentiometer_RV09
R11, R12: 10k; R_Axial_DIN0207_L6.3mm_D2.5mm_P7.62mm_Horizontal

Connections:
A1: J1.T, J4.13
A2: D7.2, J2.T, J4.14
A3: J4.1, POT_ATTACK1.1
A4: J4.2, POT_ATTACK1.2, POT_ATTACK1.3
A5: J4.3, POT_DECAY1.1
A6: J4.4, POT_DECAY1.2, POT_DECAY1.3
A7: J4.5, POT_SUSTAIN1.1
A8: J4.6, POT_SUSTAIN1.2
A9: J4.7, POT_SUSTAIN1.3
A10: J4.8, POT_RELEASE1.1
A11: J4.9, POT_RELEASE1.2, POT_RELEASE1.3
A_VCC: D6.2, J4.10
GND1: J1.S, J1.TN, J2.S, J4.11, J4.12, R11.1, R12.1
unnamed: D6.1, R11.2
unnamed: D7.1, R12.2
